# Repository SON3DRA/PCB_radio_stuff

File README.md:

# PCB_radio_stuff
pcb Kicad inerenti la radio

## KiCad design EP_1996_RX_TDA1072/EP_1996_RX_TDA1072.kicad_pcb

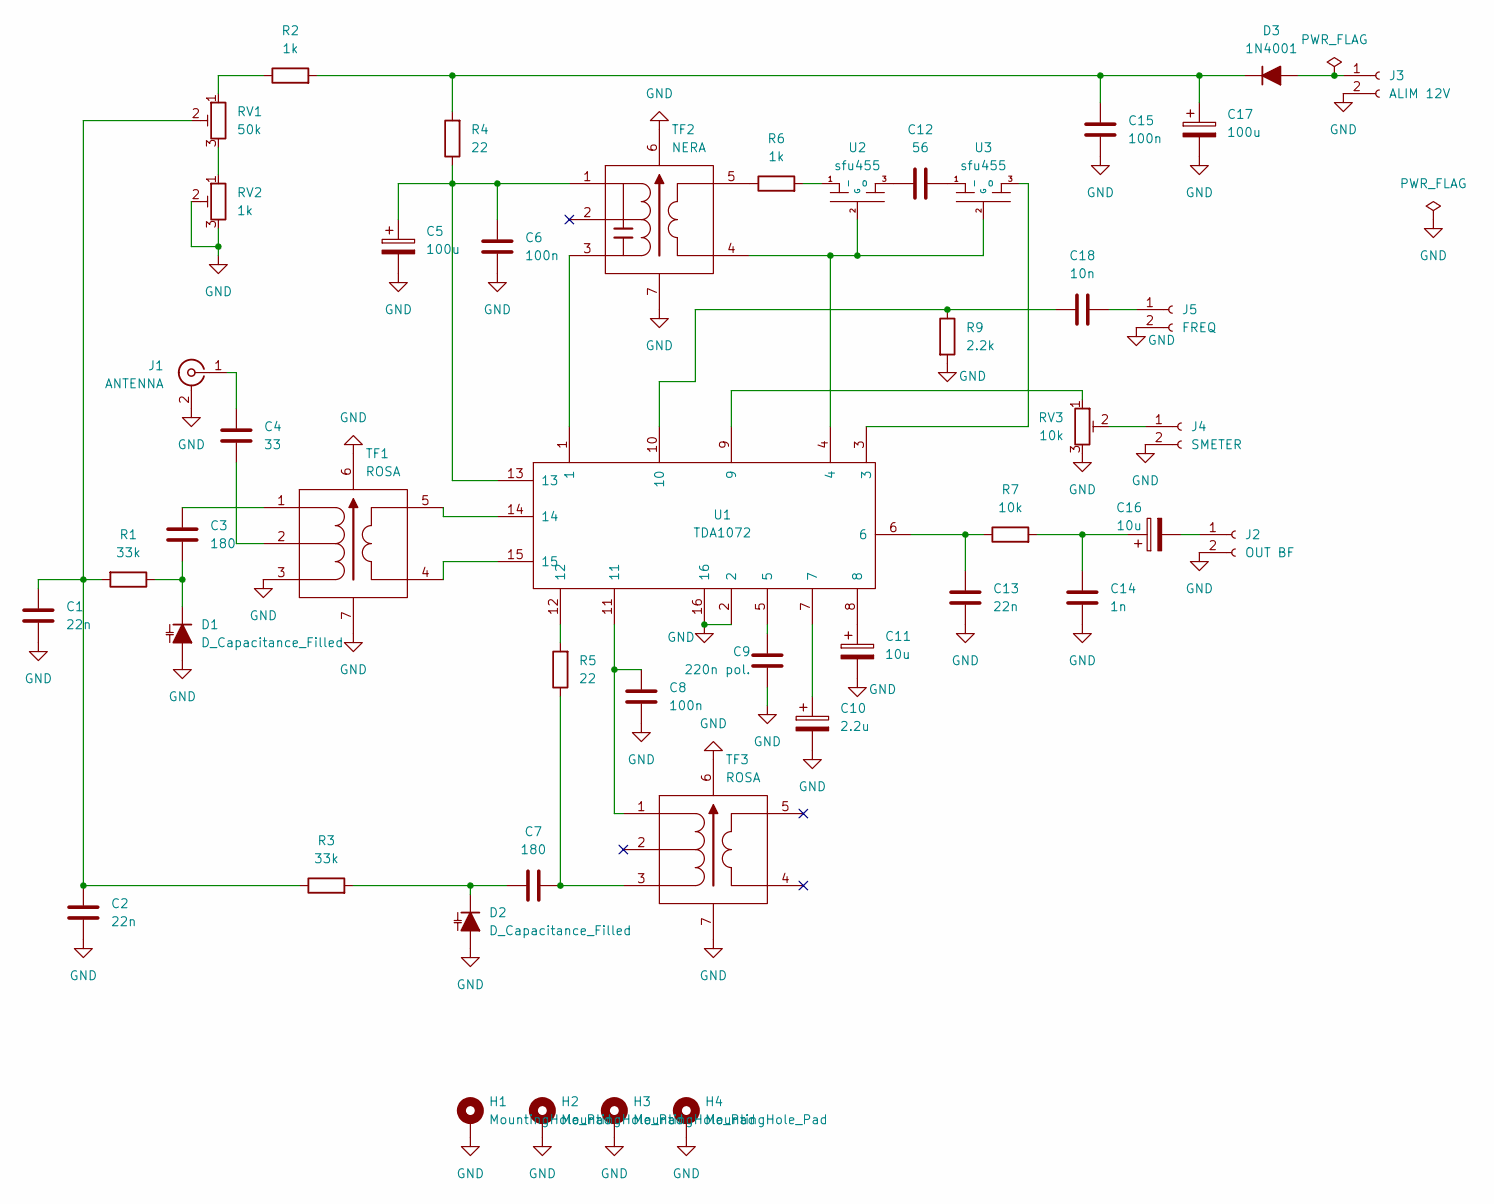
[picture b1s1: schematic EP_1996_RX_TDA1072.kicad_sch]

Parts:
C1, C2, C13: 22n; C_Disc_D4.3mm_W1.9mm_P5.00mm
C3, C7: 180; C_Disc_D4.3mm_W1.9mm_P5.00mm
C4: 33; C_Disc_D4.3mm_W1.9mm_P5.00mm
C5, C17: 100u; CP_Radial_D8.0mm_P3.80mm
C6, C8, C15: 100n; C_Disc_D4.3mm_W1.9mm_P5.00mm
C9: 220n pol.; C_Disc_D4.3mm_W1.9mm_P5.00mm
C10: 2.2u; CP_Radial_D8.0mm_P3.80mm
C11, C16: 10u; CP_Radial_D8.0mm_P3.80mm
C12: 56; C_Disc_D4.3mm_W1.9mm_P5.00mm
C14: 1n; C_Disc_D4.3mm_W1.9mm_P5.00mm
C18: 10n; C_Disc_D4.3mm_W1.9mm_P5.00mm
D1, D2: D_Capacitance_Filled; TO-92-2_Wide_KA
D3: 1N4001; D_DO-41_SOD81_P10.16mm_Horizontal
H1, H2, H3, H4: MountingHole_Pad; MountingHole_2.2mm_M2_Pad
J1: ANTENNA; SMA_Amphenol_901-144_Vertical
J2: OUT BF; PinHeader_1x02_P2.54mm_Vertical
J3: ALIM 12V; PinHeader_1x02_P2.54mm_Vertical
J4: SMETER; PinHeader_1x02_P2.54mm_Vertical
J5: FREQ; PinHeader_1x02_P2.54mm_Vertical
R1, R3: 33k; R_Axial_DIN0207_L6.3mm_D2.5mm_P10.16mm_Horizontal
R2, R6: 1k; R_Axial_DIN0207_L6.3mm_D2.5mm_P10.16mm_Horizontal
R4, R5: 22; R_Axial_DIN0207_L6.3mm_D2.5mm_P10.16mm_Horizontal
R7: 10k; R_Axial_DIN0207_L6.3mm_D2.5mm_P10.16mm_Horizontal
R9: 2.2k; R_Axial_DIN0207_L6.3mm_D2.5mm_P10.16mm_Horizontal
RV1: 50k; Potentiometer_Telpod_TVP1232
RV2: 1k; Potentiometer_Telpod_TVP1232
RV3: 10k; Potentiometer_Runtron_RM-065_Vertical
TF1, TF3: ROSA; TOKO_10K
TF2: NERA; TOKO_10K
U1: TDA1072; CERDIP-16_W7.62mm_SideBrazed_LongPads_Socket
U2, U3: sfu455; SFU455

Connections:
GND: C1.2, C2.2, C5.2, C6.2, C8.2, C9.2, C10.2, C11.2, C13.2, C14.2, C15.2, C17.2, D1.2 (A), D2.2 (A), H1.1, H2.1, H3.1, H4.1, J1.2 (Ext), J2.2, J3.2, J4.2, J5.2, R9.2, RV2.2, RV2.3, RV3.3, TF1.3, TF1.6, TF1.7, TF2.6, TF2.7, TF3.6, TF3.7, U1.2, U1.16
unnamed: C1.1, C2.1, R1.2, R3.1, RV1.2
unnamed: C3.1, TF1.1
unnamed: C4.2, TF1.2
unnamed: C5.1, C6.1, R4.1, TF2.1, U1.13
unnamed: C7.2, R5.1, TF3.3
unnamed: C8.1, TF3.1, U1.11
unnamed: C9.1, U1.5
unnamed: C10.1, U1.7
unnamed: C11.1, U1.8
unnamed: C13.1, R7.1, U1.6
unnamed: C14.1, C16.1, R7.2
unnamed: C18.1, R9.1, U1.10
unnamed: C3.2, D1.1 (K), R1.1
unnamed: C7.1, D2.1 (K), R3.2
unnamed: D3.2 (A), J3.1
unnamed: C15.1, C17.1, D3.1 (K), R2.2, R4.2
unnamed: C4.1, J1.1 (In)
unnamed: C16.2, J2.1
unnamed: J4.1, RV3.2
unnamed: C18.2, J5.1
unnamed: R2.1, RV1.1
unnamed: R5.2, U1.12
unnamed: R6.1, TF2.5
unnamed: RV1.3, RV2.1
unnamed: RV3.1, U1.9
unnamed: TF1.4, U1.15
unnamed: TF1.5, U1.14
unnamed: TF2.3, U1.1
unnamed: TF2.4, U1.4, U2.2 (G), U3.2 (G)
unnamed: R6.2, U2.1 (I)
unnamed: C12.1, U2.3 (O)
unnamed: C12.2, U3.1 (I)
unnamed: U1.3, U3.3 (O)

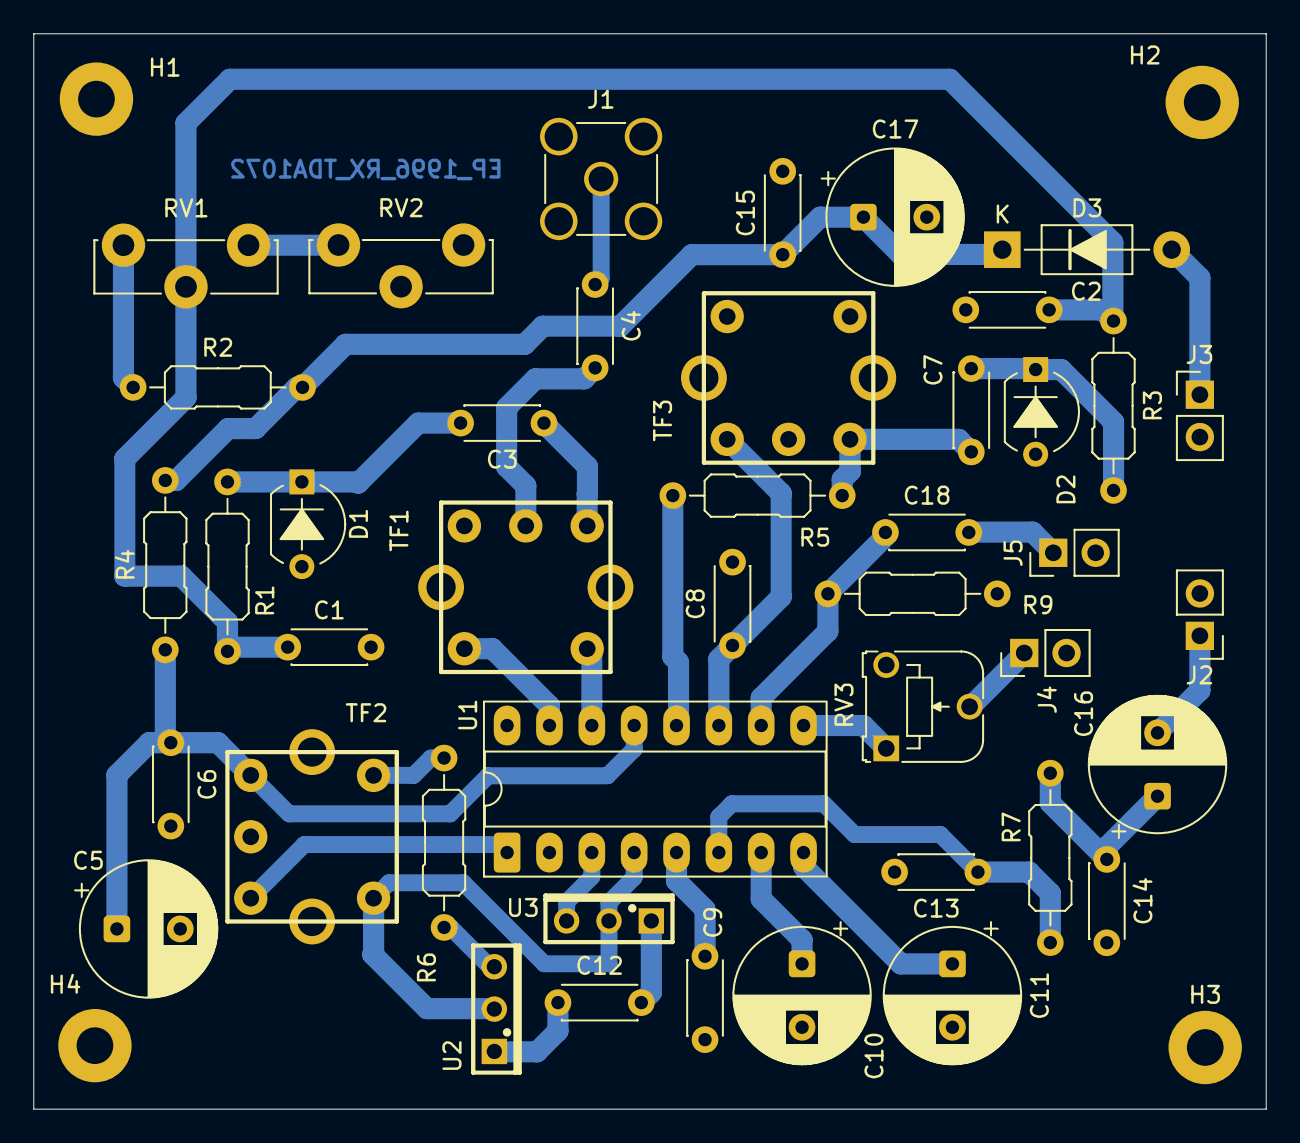
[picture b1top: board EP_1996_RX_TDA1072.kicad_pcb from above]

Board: 2 copper layers, 73.9 x 64.5 mm, 47 parts (0 on the bottom side), 34 nets.

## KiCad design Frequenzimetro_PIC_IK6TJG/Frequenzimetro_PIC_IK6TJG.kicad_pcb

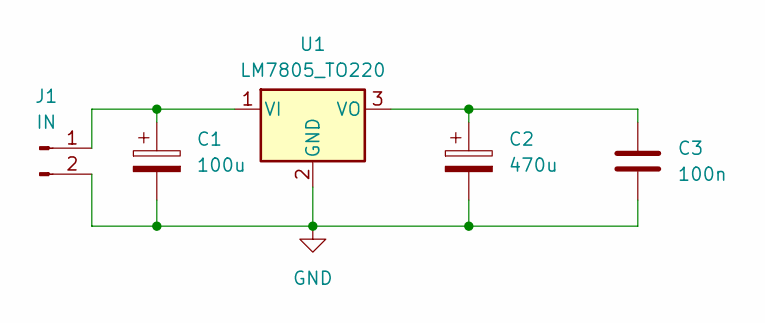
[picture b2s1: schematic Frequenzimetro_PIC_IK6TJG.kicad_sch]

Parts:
C1: 100u; CP_Radial_D6.3mm_P2.50mm
C2: 470u; CP_Radial_D6.3mm_P2.50mm
C3: 100n; C_Disc_D4.3mm_W1.9mm_P5.00mm
J1: IN; PinHeader_1x02_P2.54mm_Vertical
U1: LM7805_TO220; TO-220-3_Vertical

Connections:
GND: C1.2, C2.2, C3.2, J1.2, U1.2 (GND)
unnamed: C1.1, J1.1, U1.1 (VI)
unnamed: C2.1, C3.1, U1.3 (VO)

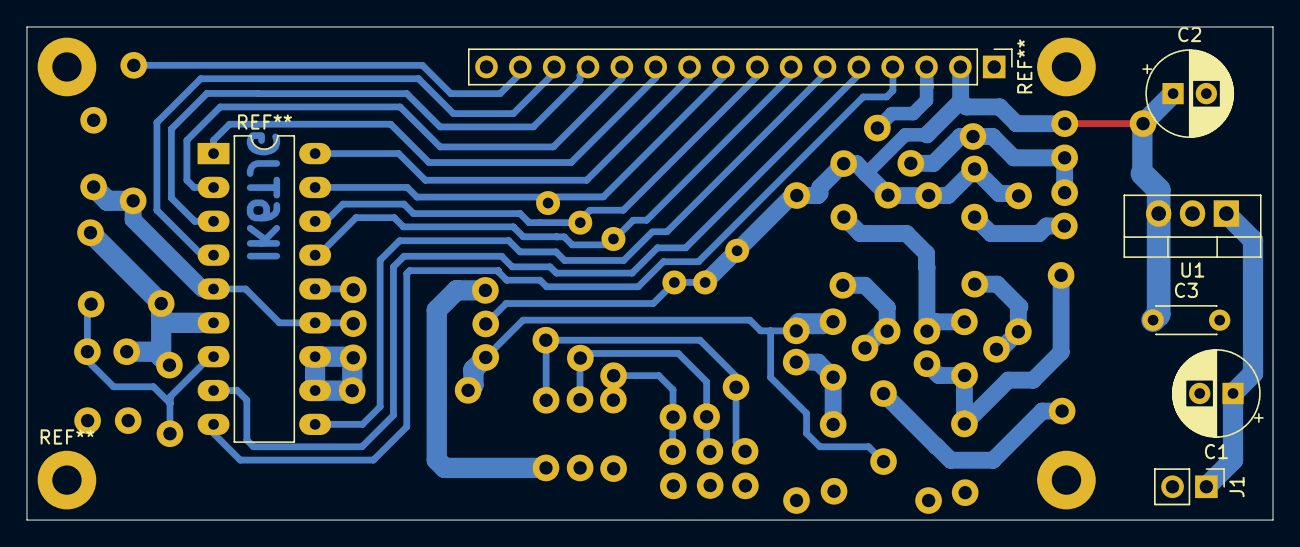
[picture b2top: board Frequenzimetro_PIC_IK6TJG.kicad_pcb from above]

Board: 2 copper layers, 93.5 x 37.0 mm, 5 parts (0 on the bottom side), 3 nets.

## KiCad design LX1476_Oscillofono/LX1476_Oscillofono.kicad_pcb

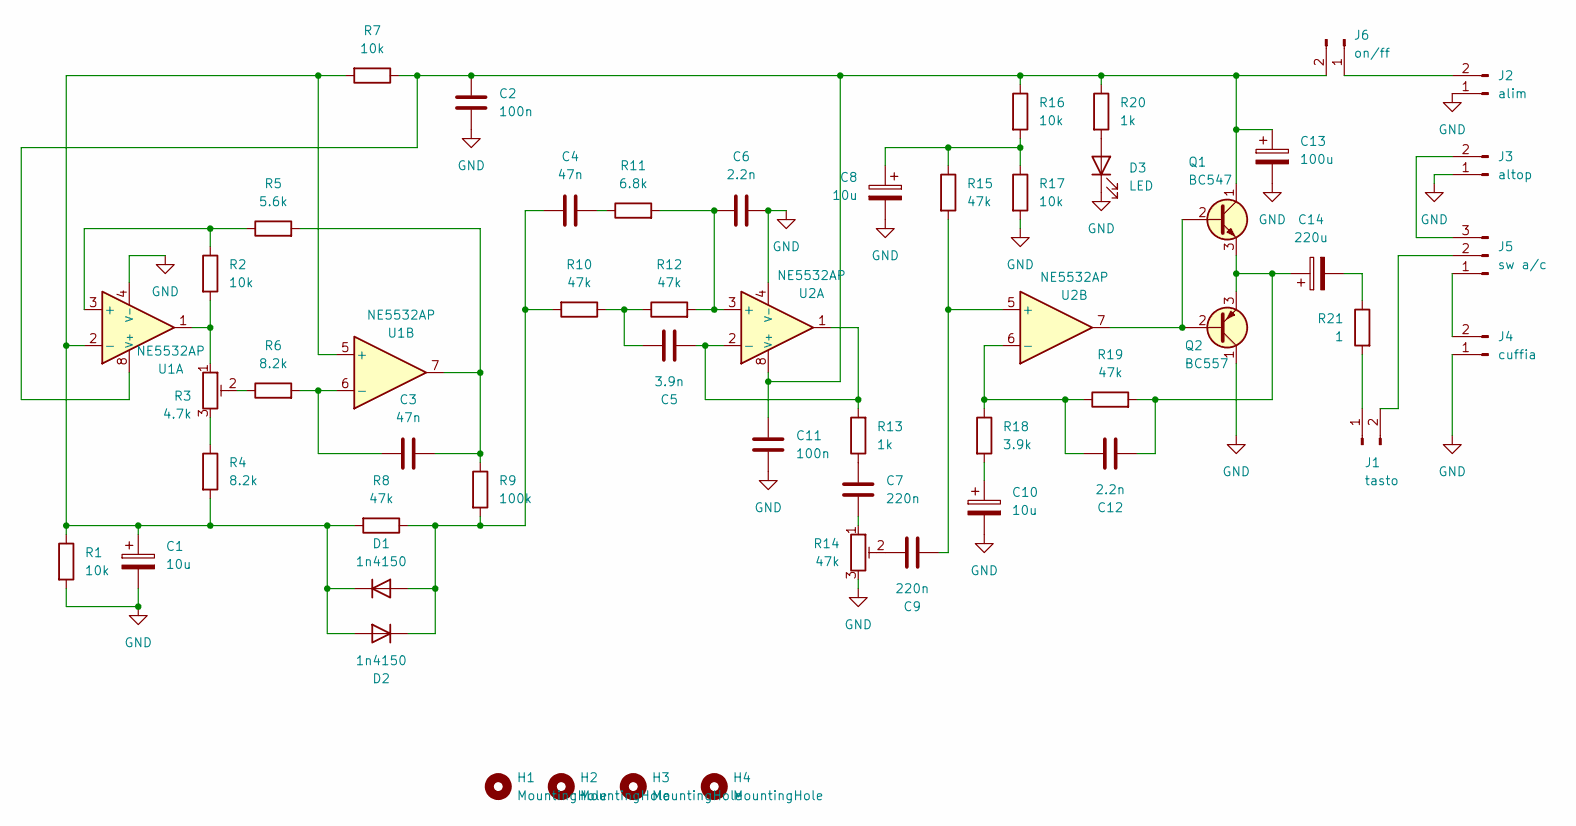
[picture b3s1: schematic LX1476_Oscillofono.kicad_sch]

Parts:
C1, C8, C10: 10u; CP_Radial_D6.3mm_P2.50mm
C2, C11: 100n; C_Disc_D7.5mm_W2.5mm_P5.00mm
C3, C4: 47n; C_Disc_D7.5mm_W2.5mm_P5.00mm
C5: 3.9n; C_Disc_D7.5mm_W2.5mm_P5.00mm
C6, C12: 2.2n; C_Disc_D7.5mm_W2.5mm_P5.00mm
C7, C9: 220n; C_Disc_D7.5mm_W2.5mm_P5.00mm
C13: 100u; CP_Radial_D6.3mm_P2.50mm
C14: 220u; CP_Radial_D6.3mm_P2.50mm
D1, D2: 1n4150; D_A-405_P7.62mm_Horizontal
D3: LED; LED_D5.0mm_Clear
H1, H2, H3, H4: MountingHole; MountingHole_2.2mm_M2_ISO14580_Pad
J1: tasto; PinHeader_1x02_P2.54mm_Vertical
J2: alim; PinHeader_1x02_P2.54mm_Vertical
J3: altop; PinHeader_1x02_P2.54mm_Vertical
J4: cuffia; PinHeader_1x02_P2.54mm_Vertical
J5: sw a/c; PinHeader_1x03_P2.54mm_Vertical
J6: on/ff; PinHeader_1x02_P2.54mm_Vertical
Q1: BC547; TO-92_Inline_Wide_CBE
Q2: BC557; TO-92_Inline_Wide_CBE
R1, R2, R7, R16, R17: 10k; R_Axial_DIN0207_L6.3mm_D2.5mm_P10.16mm_Horizontal
R3: 4.7k; Potentiometer_ACP_CA14-H2,5_Horizontal
R4, R6: 8.2k; R_Axial_DIN0207_L6.3mm_D2.5mm_P10.16mm_Horizontal
R5: 5.6k; R_Axial_DIN0207_L6.3mm_D2.5mm_P10.16mm_Horizontal
R8, R10, R12, R15, R19: 47k; R_Axial_DIN0207_L6.3mm_D2.5mm_P10.16mm_Horizontal
R9: 100k; R_Axial_DIN0207_L6.3mm_D2.5mm_P10.16mm_Horizontal
R11: 6.8k; R_Axial_DIN0207_L6.3mm_D2.5mm_P10.16mm_Horizontal
R13, R20: 1k; R_Axial_DIN0207_L6.3mm_D2.5mm_P10.16mm_Horizontal
R14: 47k; Potentiometer_ACP_CA14-H2,5_Horizontal
R18: 3.9k; R_Axial_DIN0207_L6.3mm_D2.5mm_P10.16mm_Horizontal
R21: 1; R_Axial_DIN0207_L6.3mm_D2.5mm_P10.16mm_Horizontal
U1, U2: NE5532AP; DIP-8_W7.62mm_LongPads

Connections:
GND: C1.2, C2.2, C6.2, C8.2, C10.2, C11.2, C13.2, D3.1 (K), J2.1, J3.1, J4.1, Q2.1 (C), R1.2, R14.3, R17.2, U1.4 (V-), U2.4 (V-)
unnamed: C3.2, R5.2, R9.1, U1.7
unnamed: C4.2, R11.1
unnamed: C5.1, R10.1, R12.1
unnamed: C7.1, R14.1
unnamed: C7.2, R13.1
unnamed: C8.1, R15.1, R16.2, R17.1
unnamed: C9.2, R14.2
unnamed: C10.1, R18.2
unnamed: C14.2, R21.1
unnamed: C4.1, D1.2 (A), D2.1 (K), R8.1, R9.2, R10.2
unnamed: C1.1, D1.1 (K), D2.2 (A), R1.1, R4.2, R7.2, R8.2, U1.2 (-), U1.5 (+)
unnamed: D3.2 (A), R20.2
unnamed: J1.1, R21.2
unnamed: J1.2, J5.2
unnamed: J2.2, J6.1
unnamed: J3.2, J5.3
unnamed: J4.2, J5.1
unnamed: C2.1, C11.1, C13.1, J6.2, Q1.1 (C), R7.1, R16.1, R20.1, U1.8 (V+), U2.8 (V+)
unnamed: Q1.2 (B), Q2.2 (B), U2.7
unnamed: C12.1, C14.1, Q1.3 (E), Q2.3 (E), R19.2
unnamed: R2.2, R3.1, U1.1
unnamed: R3.2, R6.1
unnamed: R3.3, R4.1
unnamed: R2.1, R5.1, U1.3 (+)
unnamed: C3.1, R6.2, U1.6 (-)
unnamed: C6.1, R11.2, R12.2, U2.3 (+)
unnamed: C5.2, R13.2, U2.1, U2.2 (-)
unnamed: C9.1, R15.2, U2.5 (+)
unnamed: C12.2, R18.1, R19.1, U2.6 (-)

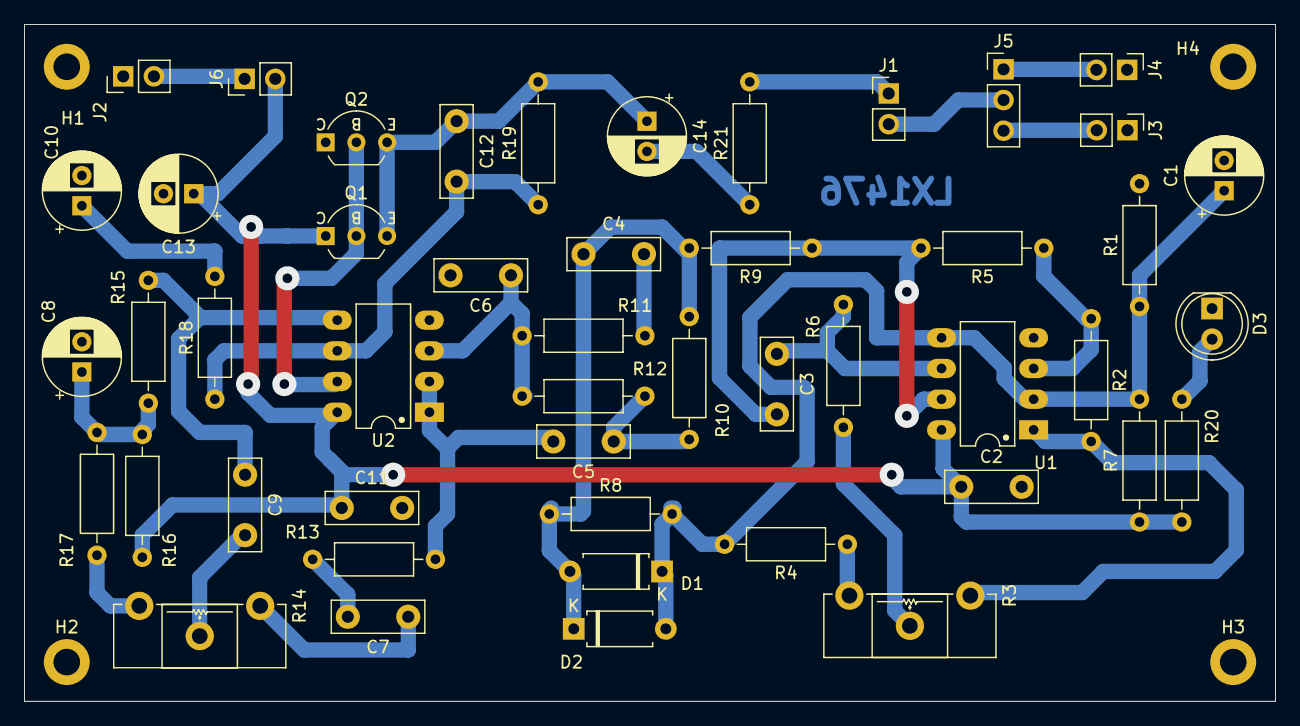
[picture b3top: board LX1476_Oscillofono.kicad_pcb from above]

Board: 2 copper layers, 103.5 x 56.0 mm, 52 parts (0 on the bottom side), 30 nets.

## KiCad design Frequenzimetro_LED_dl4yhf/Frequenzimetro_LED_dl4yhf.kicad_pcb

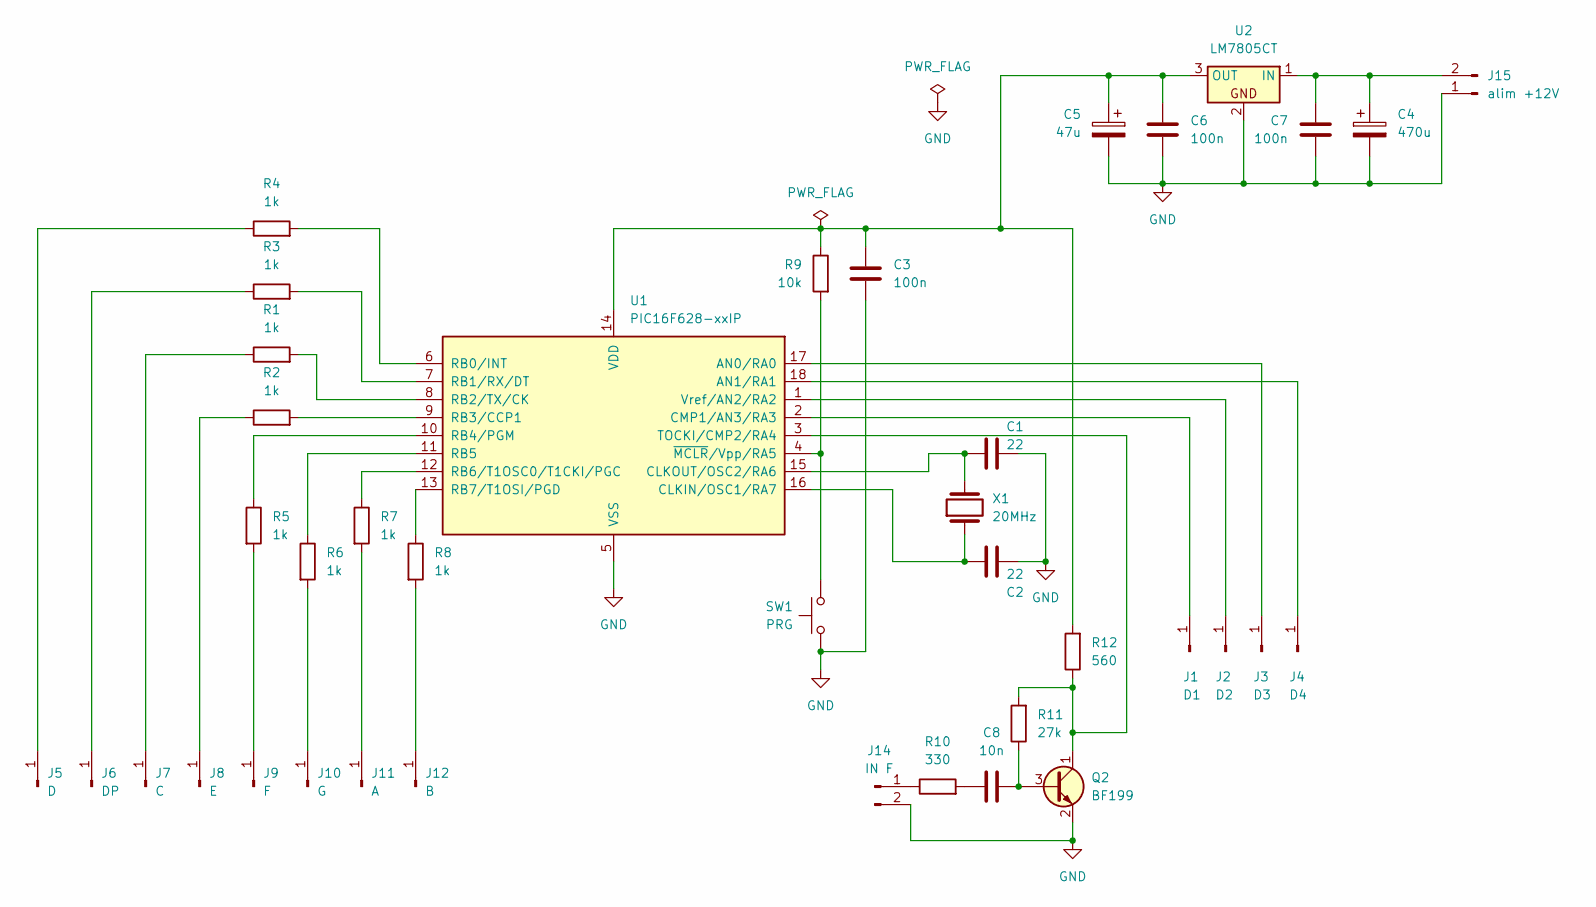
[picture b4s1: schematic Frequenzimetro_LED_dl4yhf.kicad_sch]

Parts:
C1, C2: 22; C_Disc_D5.0mm_W2.5mm_P5.00mm
C3, C6, C7: 100n; C_Disc_D5.0mm_W2.5mm_P5.00mm
C4: 470u; CP_Radial_D8.0mm_P3.50mm
C5: 47u; CP_Radial_D8.0mm_P3.50mm
C8: 10n; C_Disc_D5.0mm_W2.5mm_P5.00mm
J1: D1; PinHeader_1x01_P2.54mm_Vertical
J2: D2; PinHeader_1x01_P2.54mm_Vertical
J3: D3; PinHeader_1x01_P2.54mm_Vertical
J4: D4; PinHeader_1x01_P2.54mm_Vertical
J5: D; PinHeader_1x01_P2.54mm_Vertical
J6: DP; PinHeader_1x01_P2.54mm_Vertical
J7: C; PinHeader_1x01_P2.54mm_Vertical
J8: E; PinHeader_1x01_P2.54mm_Vertical
J9: F; PinHeader_1x01_P2.54mm_Vertical
J10: G; PinHeader_1x01_P2.54mm_Vertical
J11: A; PinHeader_1x01_P2.54mm_Vertical
J12: B; PinHeader_1x01_P2.54mm_Vertical
J14: IN F; PinHeader_1x02_P2.54mm_Vertical
J15: alim +12V; PinHeader_1x02_P2.54mm_Vertical
Q2: BF199; TO-92_Wide_CEB
R1, R2, R3, R4, R5, R6, R7, R8: 1k; R_Axial_DIN0411_L9.9mm_D3.6mm_P5.08mm_Vertical
R9: 10k; R_Axial_DIN0207_L6.3mm_D2.5mm_P10.16mm_Horizontal
R10: 330; R_Axial_DIN0207_L6.3mm_D2.5mm_P10.16mm_Horizontal
R11: 27k; R_Axial_DIN0411_L9.9mm_D3.6mm_P5.08mm_Vertical
R12: 560; R_Axial_DIN0207_L6.3mm_D2.5mm_P10.16mm_Horizontal
SW1: PRG; SW_PUSH_6mm
U1: PIC16F628-xxIP; DIP-18_W7.62mm_Socket_LongPads
U2: LM7805CT; TO-220-3_Vertical
X1: 20MHz; Crystal_HC18-U_Vertical

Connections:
GND: C1.2, C2.2, C3.2, C4.2, C5.2, C6.2, C7.2, J14.2, J15.1, Q2.2 (E), SW1.2, U1.5 (VSS), U2.2
unnamed: C8.1, R10.2
unnamed: J1.1, U1.2 (CMP1/AN3/RA3)
unnamed: J2.1, U1.1 (Vref/AN2/RA2)
unnamed: J3.1, U1.17 (AN0/RA0)
unnamed: J4.1, U1.18 (AN1/RA1)
unnamed: J5.1, R4.1
unnamed: J6.1, R3.1
unnamed: J7.1, R1.1
unnamed: J8.1, R2.1
unnamed: J9.1, R5.2
unnamed: J10.1, R6.2
unnamed: J11.1, R7.2
unnamed: J12.1, R8.2
unnamed: J14.1, R10.1
unnamed: C4.1, C7.1, J15.2, U2.1 (IN)
unnamed: C8.2, Q2.3 (B), R11.1
unnamed: Q2.1 (C), R11.2, R12.1, U1.3 (TOCKI/CMP2/RA4)
unnamed: C2.1, U1.16 (CLKIN/OSC1/RA7), X1.1
unnamed: C1.1, U1.15 (CLKOUT/OSC2/RA6), X1.2
unnamed: R4.2, U1.6 (RB0/INT)
unnamed: R3.2, U1.7 (RB1/RX/DT)
unnamed: R1.2, U1.8 (RB2/TX/CK)
unnamed: R2.2, U1.9 (RB3/CCP1)
unnamed: R5.1, U1.10 (RB4/PGM)
unnamed: R6.1, U1.11 (RB5)
unnamed: R7.1, U1.12 (RB6/T1OSC0/T1CKI/PGC)
unnamed: R8.1, U1.13 (RB7/T1OSI/PGD)
unnamed: C3.1, C5.1, C6.1, R9.1, R12.2, U1.14 (VDD), U2.3 (OUT)
unnamed: R9.2, SW1.1, U1.4 (~MCLR/Vpp/RA5)

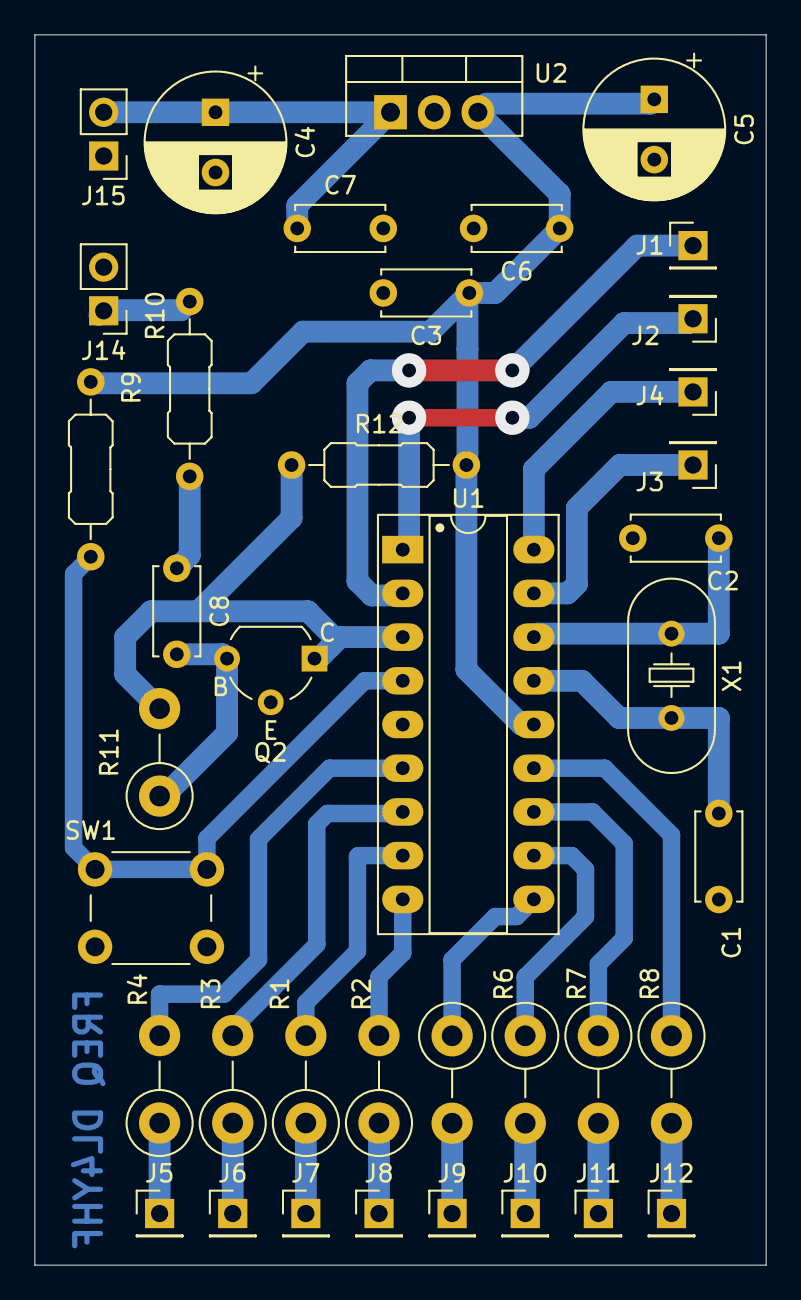
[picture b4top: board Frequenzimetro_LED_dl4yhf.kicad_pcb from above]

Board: 2 copper layers, 42.5 x 71.5 mm, 39 parts (0 on the bottom side), 30 nets.

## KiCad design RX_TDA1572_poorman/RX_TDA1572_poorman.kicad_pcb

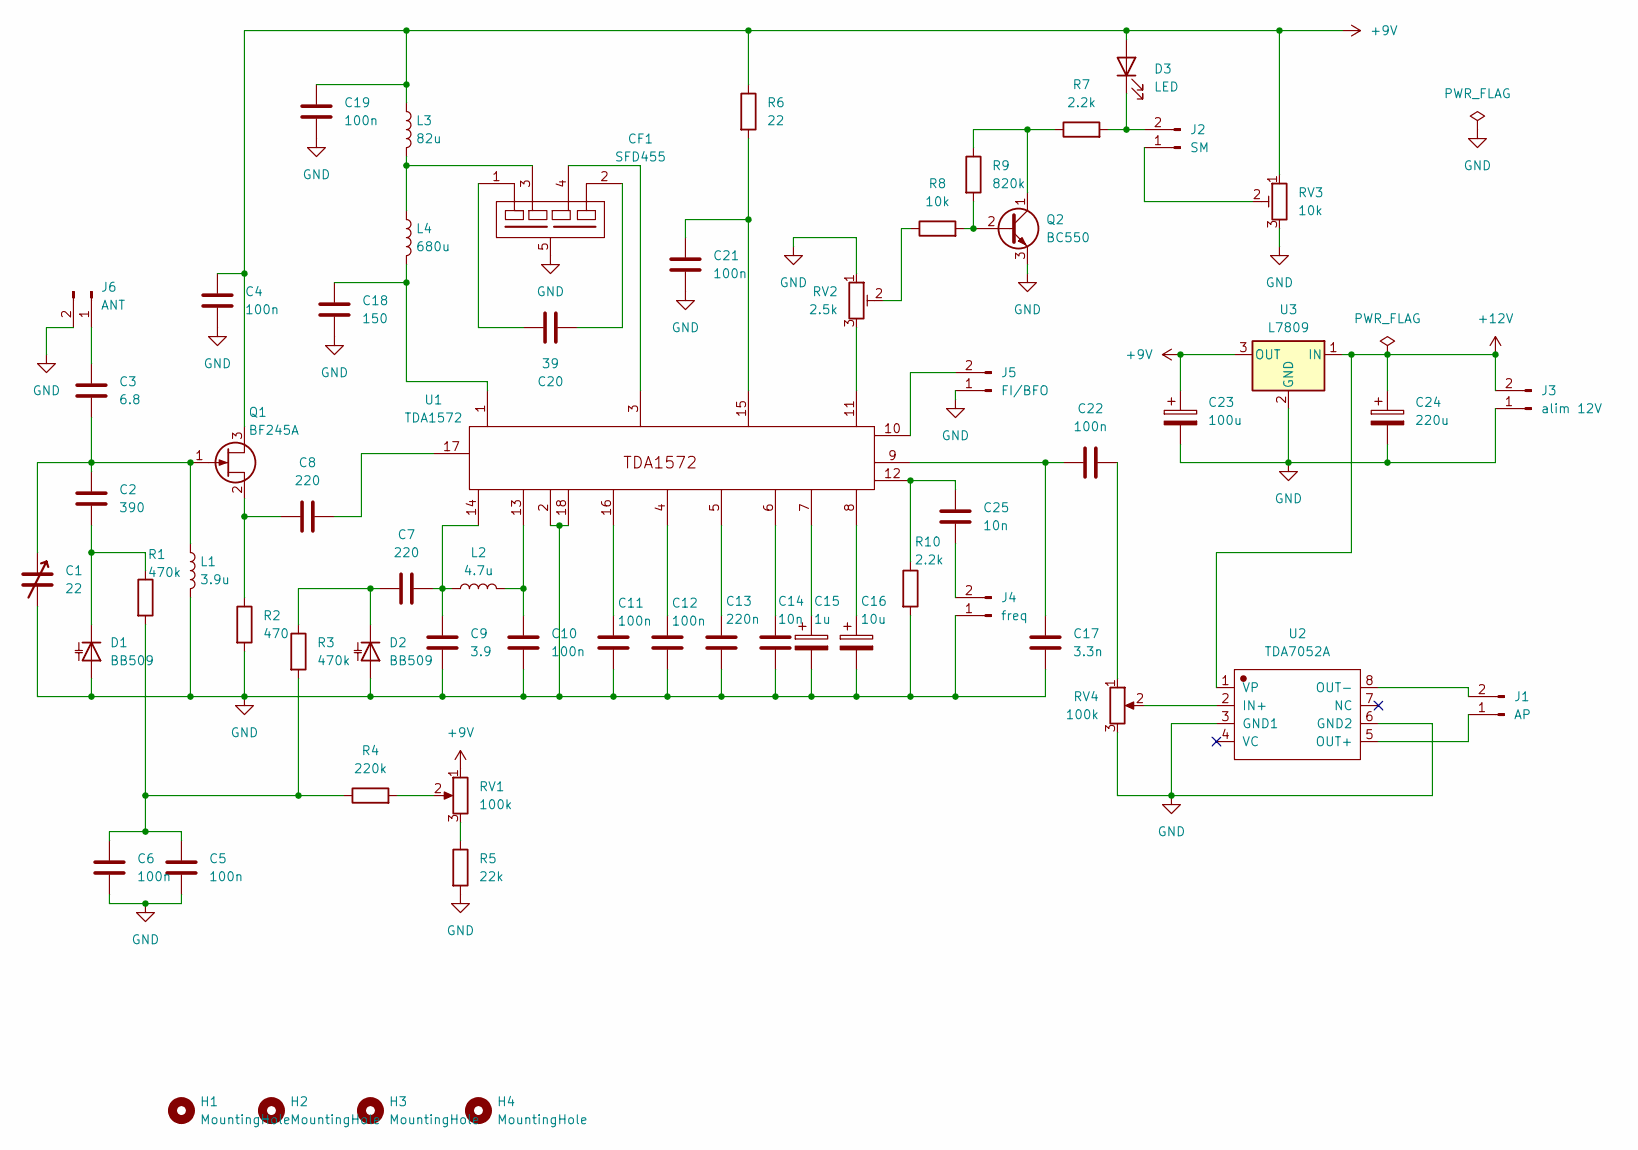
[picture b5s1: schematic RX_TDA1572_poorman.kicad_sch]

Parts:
C1: 22; Potentiometer_Runtron_RM-065_Vertical
C2: 390; C_Rect_L9.0mm_W3.4mm_P7.50mm_MKT
C3: 6.8; C_Rect_L9.0mm_W3.4mm_P7.50mm_MKT
C4, C5, C6, C10, C11, C12, C19, C21, C22: 100n; C_Rect_L9.0mm_W3.4mm_P7.50mm_MKT
C7, C8: 220; C_Rect_L9.0mm_W3.4mm_P7.50mm_MKT
C9: 3.9; C_Rect_L9.0mm_W3.4mm_P7.50mm_MKT
C13: 220n; C_Rect_L9.0mm_W3.4mm_P7.50mm_MKT
C14, C25: 10n; C_Rect_L9.0mm_W3.4mm_P7.50mm_MKT
C15: 1u; CP_Radial_D5.0mm_P2.50mm
C16: 10u; CP_Radial_D5.0mm_P2.50mm
C17: 3.3n; C_Rect_L9.0mm_W3.4mm_P7.50mm_MKT
C18: 150; C_Rect_L9.0mm_W3.4mm_P7.50mm_MKT
C20: 39; C_Rect_L9.0mm_W3.4mm_P7.50mm_MKT
C23: 100u; CP_Radial_D8.0mm_P5.00mm
C24: 220u; CP_Radial_D8.0mm_P5.00mm
CF1: SFD455
D1, D2: BB509; D_A-405_P7.62mm_Horizontal
D3: LED; LED_D5.0mm_Clear
H1, H2, H3, H4: MountingHole; MountingHole_2.5mm_Pad
J1: AP; PinHeader_1x02_P2.54mm_Vertical
J2: SM; PinHeader_1x02_P2.54mm_Vertical
J3: alim 12V; PinHeader_1x02_P2.54mm_Vertical
J4: freq; PinHeader_1x02_P2.54mm_Vertical
J5: FI/BFO; PinHeader_1x02_P2.54mm_Vertical
J6: ANT; PinHeader_1x02_P2.54mm_Vertical
L1: 3.9u; L_Axial_L7.0mm_D3.3mm_P12.70mm_Horizontal_Fastron_MICC
L2: 4.7u; L_Axial_L7.0mm_D3.3mm_P12.70mm_Horizontal_Fastron_MICC
L3: 82u; L_Axial_L7.0mm_D3.3mm_P12.70mm_Horizontal_Fastron_MICC
L4: 680u; L_Axial_L7.0mm_D3.3mm_P12.70mm_Horizontal_Fastron_MICC
Q1: BF245A; TO-92_Inline_Wide
Q2: BC550; TO-92_Inline_Wide
R1, R3: 470k; R_Axial_DIN0207_L6.3mm_D2.5mm_P10.16mm_Horizontal
R2: 470; R_Axial_DIN0207_L6.3mm_D2.5mm_P10.16mm_Horizontal
R4: 220k; R_Axial_DIN0207_L6.3mm_D2.5mm_P10.16mm_Horizontal
R5: 22k; R_Axial_DIN0207_L6.3mm_D2.5mm_P10.16mm_Horizontal
R6: 22; R_Axial_DIN0207_L6.3mm_D2.5mm_P10.16mm_Horizontal
R7, R10: 2.2k; R_Axial_DIN0207_L6.3mm_D2.5mm_P10.16mm_Horizontal
R8: 10k; R_Axial_DIN0207_L6.3mm_D2.5mm_P10.16mm_Horizontal
R9: 820k; R_Axial_DIN0207_L6.3mm_D2.5mm_P10.16mm_Horizontal
RV1, RV4: 100k; Potentiometer_Piher_PT-15-H01_Horizontal
RV2: 2.5k; Potentiometer_Piher_PT-10-V10_Vertical
RV3: 10k; Potentiometer_Piher_PT-10-V10_Vertical
U1: TDA1572; DIP-18_W7.62mm_Socket_LongPads
U2: TDA7052A; DIP-8_W7.62mm_Socket_LongPads
U3: L7809; TO-220-3_Vertical

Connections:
+9V: C4.1, C19.1, C23.1, D3.2 (A), L3.1, Q1.3 (D), R6.1, RV1.1, RV3.1, U3.3 (OUT)
+12V: C24.1, J3.2, U2.1 (VP), U3.1 (IN)
GND: C1.2, C4.2, C5.2, C6.2, C9.1, C10.1, C11.1, C12.1, C13.1, C14.1, C15.2, C16.2, C17.2, C18.2, C19.2, C21.2, C23.2, C24.2, CF1.5 (COMUN), D1.2 (A), D2.2 (A), J3.1, J4.1, J5.1, J6.2, L1.2, Q2.3 (E), R2.2, R5.2, R10.2, RV2.1, RV3.3, RV4.3, U1.2, U1.18, U2.3 (GND1), U2.6 (GND2), U3.2 (GND)
unnamed: C5.1, C6.1, R1.2, R3.2, R4.1
unnamed: C7.2, C9.2, L2.1, U1.14
unnamed: C8.2, U1.17
unnamed: C10.2, L2.2, U1.13
unnamed: C11.2, U1.16
unnamed: C12.2, U1.4
unnamed: C13.2, U1.5
unnamed: C14.2, U1.6
unnamed: C15.1, U1.7
unnamed: C16.1, U1.8
unnamed: C17.1, C22.1, U1.9
unnamed: C18.1, L4.2, U1.1
unnamed: C21.1, R6.2, U1.15
unnamed: C22.2, RV4.1
unnamed: C25.1, R10.1, U1.12
unnamed: CF1.3 (Ca), L3.2, L4.1
unnamed: CF1.4 (Cb), U1.3
unnamed: C20.1, CF1.1 (IN)
unnamed: C20.2, CF1.2 (OUT)
unnamed: C2.2, D1.1 (K), R1.1
unnamed: C7.1, D2.1 (K), R3.1
unnamed: D3.1 (K), J2.2, R7.2
unnamed: J1.1, U2.5 (OUT+)
unnamed: J1.2, U2.8 (OUT-)
unnamed: J2.1, RV3.2
unnamed: C25.2, J4.2
unnamed: J5.2, U1.10
unnamed: C3.1, J6.1
unnamed: C1.1, C2.1, C3.2, L1.1, Q1.1 (G)
unnamed: C8.1, Q1.2 (S), R2.1
unnamed: Q2.2 (B), R8.2, R9.2
unnamed: Q2.1 (C), R7.1, R9.1
unnamed: R4.2, RV1.2
unnamed: R5.1, RV1.3
unnamed: R8.1, RV2.2
unnamed: RV2.3, U1.11
unnamed: RV4.2, U2.2 (IN+)

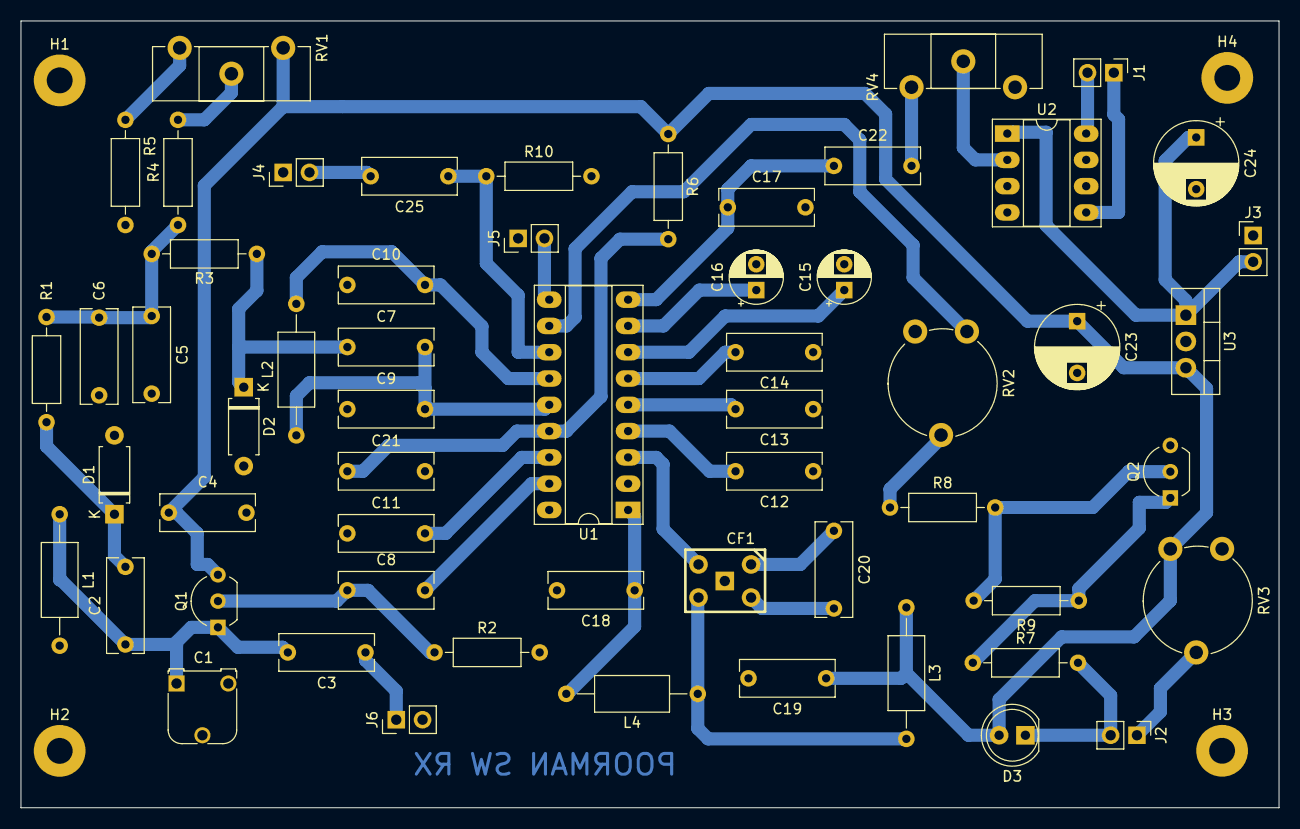
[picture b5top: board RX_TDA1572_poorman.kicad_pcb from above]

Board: 2 copper layers, 121.5 x 76.0 mm, 62 parts (0 on the bottom side), 40 nets.

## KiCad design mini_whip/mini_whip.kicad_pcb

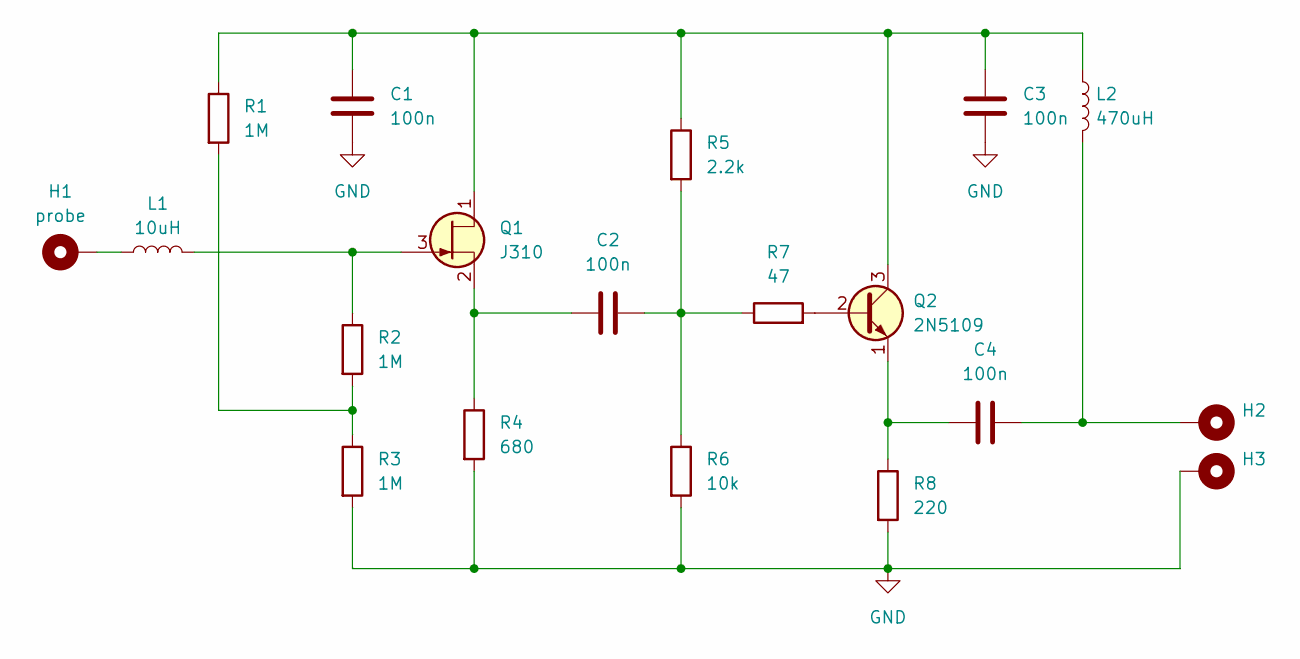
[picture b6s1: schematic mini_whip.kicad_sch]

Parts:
C1, C2, C3, C4: 100n; C_Disc_D4.3mm_W1.9mm_P5.00mm
H1: probe; MountingHole_2.2mm_M2_Pad
H2, H3: MountingHole_Pad; MountingHole_2.2mm_M2_Pad
L1: 10uH; L_Axial_L5.3mm_D2.2mm_P7.62mm_Horizontal_Vishay_IM-1
L2: 470uH; L_Axial_L5.3mm_D2.2mm_P7.62mm_Horizontal_Vishay_IM-1
Q1: J310; TO-92L_Wide
Q2: 2N5109; TO-39-3
R1, R2, R3: 1M; R_Axial_DIN0204_L3.6mm_D1.6mm_P7.62mm_Horizontal
R4: 680; R_Axial_DIN0204_L3.6mm_D1.6mm_P7.62mm_Horizontal
R5: 2.2k; R_Axial_DIN0204_L3.6mm_D1.6mm_P7.62mm_Horizontal
R6: 10k; R_Axial_DIN0204_L3.6mm_D1.6mm_P7.62mm_Horizontal
R7: 47; R_Axial_DIN0204_L3.6mm_D1.6mm_P7.62mm_Horizontal
R8: 220; R_Axial_DIN0204_L3.6mm_D1.6mm_P7.62mm_Horizontal

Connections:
GND: C1.1, C3.2, H3.1, R3.2, R4.2, R6.2, R8.2
unnamed: C2.2, R5.2, R6.1, R7.1
unnamed: C4.2, H2.1, L2.2
unnamed: H1.1, L1.1
unnamed: C1.2, C3.1, L2.1, Q1.1 (D), Q2.3 (C), R1.1, R5.1
unnamed: L1.2, Q1.3 (G), R2.1
unnamed: C2.1, Q1.2 (S), R4.1
unnamed: Q2.2 (B), R7.2
unnamed: C4.1, Q2.1 (E), R8.1
unnamed: R1.2, R2.2, R3.1

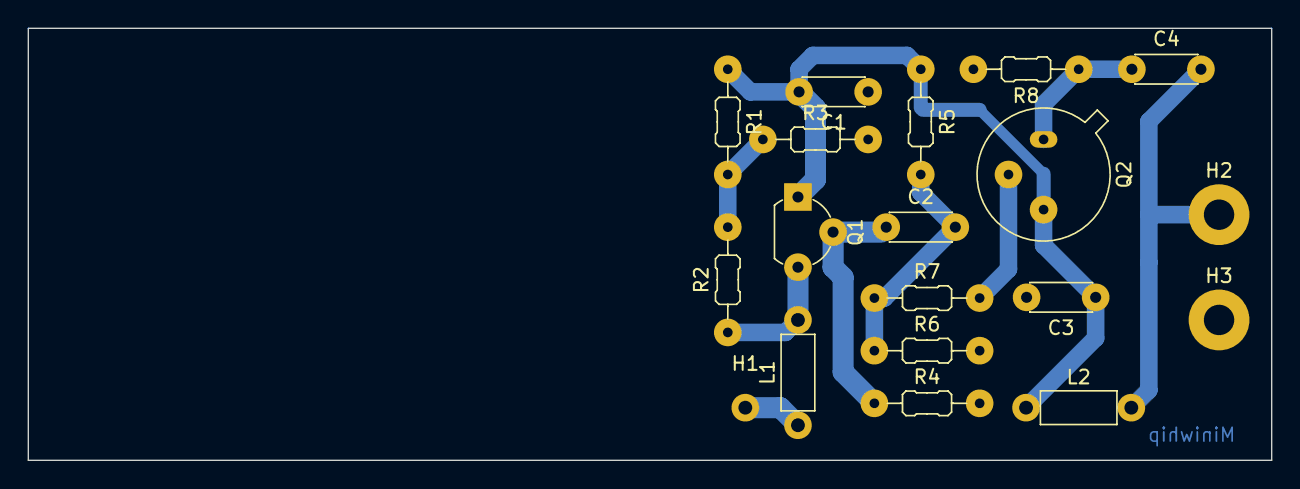
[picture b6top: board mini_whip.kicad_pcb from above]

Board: 2 copper layers, 90.0 x 31.3 mm, 19 parts (0 on the bottom side), 10 nets.

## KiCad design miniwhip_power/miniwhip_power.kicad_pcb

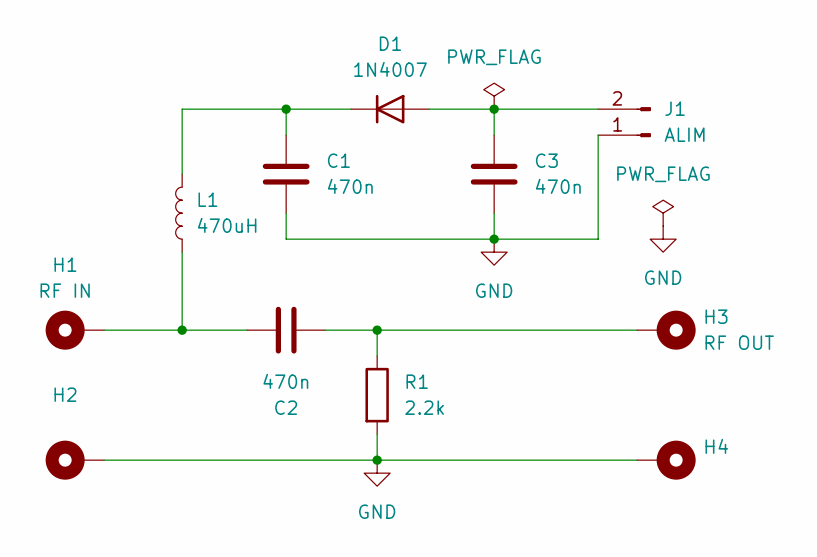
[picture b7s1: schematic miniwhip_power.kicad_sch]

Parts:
C1, C2, C3: 470n; C_Disc_D4.3mm_W1.9mm_P5.00mm
D1: 1N4007; D_A-405_P10.16mm_Horizontal
H1: RF IN; MountingHole_2.2mm_M2_Pad
H2, H4: MountingHole_Pad; MountingHole_2.2mm_M2_Pad
H3: RF OUT; MountingHole_2.2mm_M2_Pad
J1: ALIM; PinHeader_1x02_P2.54mm_Vertical
L1: 470uH; L_Axial_L5.3mm_D2.2mm_P7.62mm_Horizontal_Vishay_IM-1
R1: 2.2k; R_Axial_DIN0204_L3.6mm_D1.6mm_P7.62mm_Horizontal

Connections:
GND: C1.2, C3.1, H2.1, H4.1, J1.1, R1.2
unnamed: C2.1, H1.1, L1.1
unnamed: C2.2, H3.1, R1.1
unnamed: C3.2, D1.2 (A), J1.2
unnamed: C1.1, D1.1 (K), L1.2

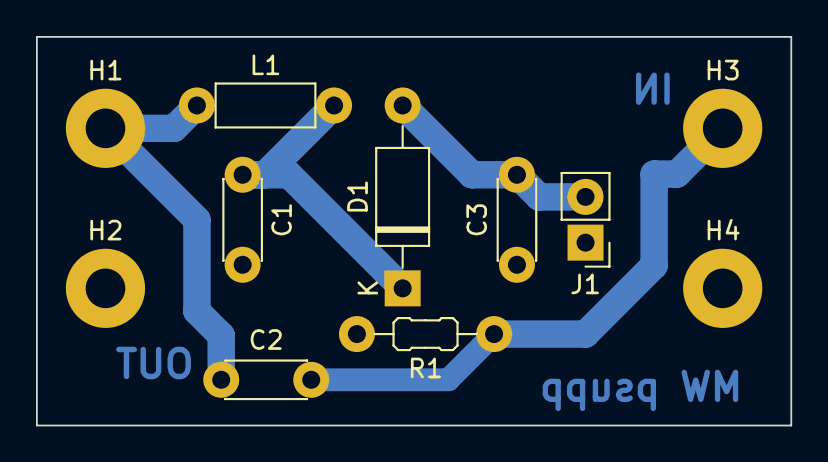
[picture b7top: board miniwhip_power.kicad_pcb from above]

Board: 2 copper layers, 41.9 x 21.6 mm, 11 parts (0 on the bottom side), 5 nets.

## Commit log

2024-11-07 Add files via upload
    RX onde corte da Elektor 10/1999.
    Pcb di dimensioni maggiori rispetto all'originale, per avere più spazio per le sperimentazioni.
2024-11-16 Add files via upload
    Frequenzimetro di DL4YHF, 4 cifre e preamplificatore d'ingresso
2024-11-16 Add files via upload
    Oscillofono Nuova Elettronica LX1476 riv.207
2024-11-16 Add files via upload
    Frequenzimetro con visualizzazione della lunghezza d'onda, LCD 16x2 e PIC 16F84 di IK6TJG
2025-07-08 Add files via upload
    PCB Kicad RX con TDA1072 da Electronics Project inverno 1996
